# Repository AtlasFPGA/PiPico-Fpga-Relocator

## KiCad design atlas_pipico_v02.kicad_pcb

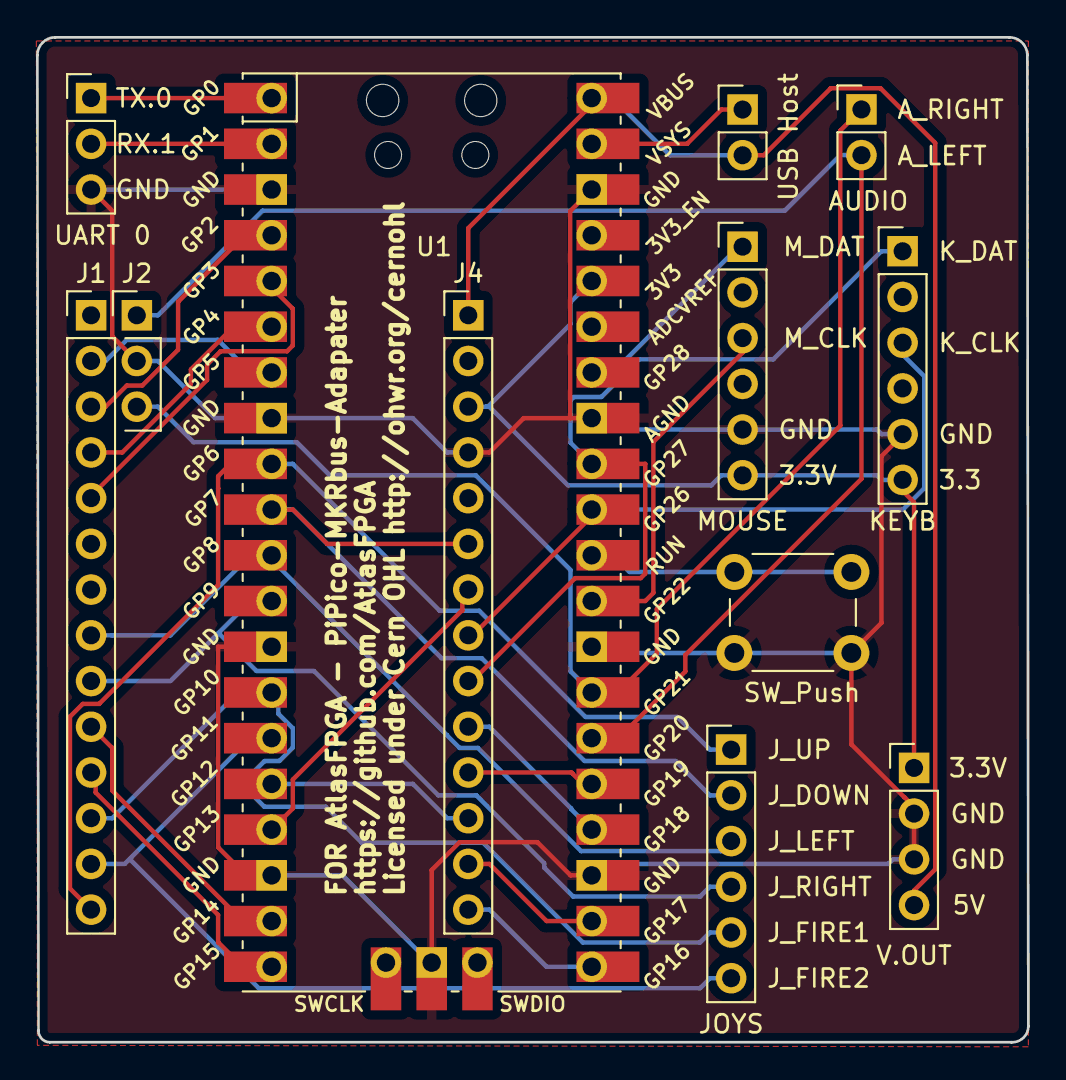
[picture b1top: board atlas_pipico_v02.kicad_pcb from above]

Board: 2 copper layers, 55.1 x 55.8 mm, 12 parts (0 on the bottom side), 31 nets.

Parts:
J1, J4: Conn_01x14; PinHeader_1x14_P2.54mm_Vertical
J2: Conn_01x03; PinHeader_1x03_P2.54mm_Vertical
J3: Conn_01x02; PinHeader_1x02_P2.54mm_Vertical
J5: UART 0; PinHeader_1x03_P2.54mm_Vertical
J6, J8, J9: Conn_01x06; PinHeader_1x06_P2.54mm_Vertical
J7: Conn_01x04; PinHeader_1x04_P2.54mm_Vertical
JP1: USB Host; PinHeader_1x02_P2.54mm_Vertical
SW1: SW_Push; SW_PUSH_6mm
U1: Pico; RPi_Pico_SMD_TH

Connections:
+3.3V: J4.3, J6.6, J7.1, J8.6, U1.36 (3V3)
+5V: J4.1, J7.4, JP1.2 (B), U1.40 (VBUS)
/GPIO0_TX: J5.1, U1.1 (GPIO0)
/GPIO1_RX: J5.2, U1.2 (GPIO1)
GND: J2.2, J4.4, J5.3, J6.5, J7.2, J7.3, J8.5, SW1.2, U1.3 (GND), U1.8 (GND), U1.13 (GND), U1.18 (GND), U1.23 (GND), U1.28 (GND), U1.33 (AGND), U1.38 (GND), U1.42 (GND)
J14_JOY_UP: J1.14, J9.1, U1.9 (GPIO6)
K2_KDAT: J4.9, J8.1, U1.32 (GPIO27_ADC1)
K15_JOY_FIRE1: J1.12, J9.5, U1.14 (GPIO10)
K16_JOY_FIRE2: J1.13, J9.6, U1.15 (GPIO11)
L2_KCLK: J4.8, J8.3, U1.31 (GPIO26_ADC0)
MOUSE_CLK: J6.3, U1.29 (GPIO22)
MOUSE_DAT: J6.1, U1.34 (GPIO28_ADC2)
N16_JOY_RIGHT: J1.9, J9.4, U1.12 (GPIO9)
unnamed: JP1.1 (A), U1.39 (VSYS)
unnamed: SW1.1, U1.30 (RUN)
R1_JOY_DOWN: J4.6, J9.2, U1.10 (GPIO7)
R11_RIGHT: J2.3, J3.1, U1.27 (GPIO21)
R12_SD_CS: J1.2, U1.7 (GPIO5)
R13_SD_MISO: J1.4, U1.6 (GPIO4)
T12_LEFT: J2.1, J3.2, U1.26 (GPIO20)
T13_SD_CLK: J1.3, U1.4 (GPIO2)
T14_SD_MOSI: J1.5, U1.5 (GPIO3)
T15_JOY_LEFT: J1.8, J9.3, U1.11 (GPIO8)
TMDSC_N: J1.11, U1.20 (GPIO15)
TMDSC_P: J1.10, U1.19 (GPIO14)
TMDS_0_N: J4.7, U1.17 (GPIO13)
TMDS_0_P: J4.12, U1.16 (GPIO12)
TMDS_1_N: J4.11, U1.25 (GPIO19)
TMDS_1_P: J4.10, U1.24 (GPIO18)
TMDS_2_N: J4.13, U1.22 (GPIO17)
TMDS_2_P: J4.14, U1.21 (GPIO16)

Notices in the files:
atlas_pipico_v02.kicad_pcb:
Licensed under Cern OHL http://ohwr.org/cernohl
